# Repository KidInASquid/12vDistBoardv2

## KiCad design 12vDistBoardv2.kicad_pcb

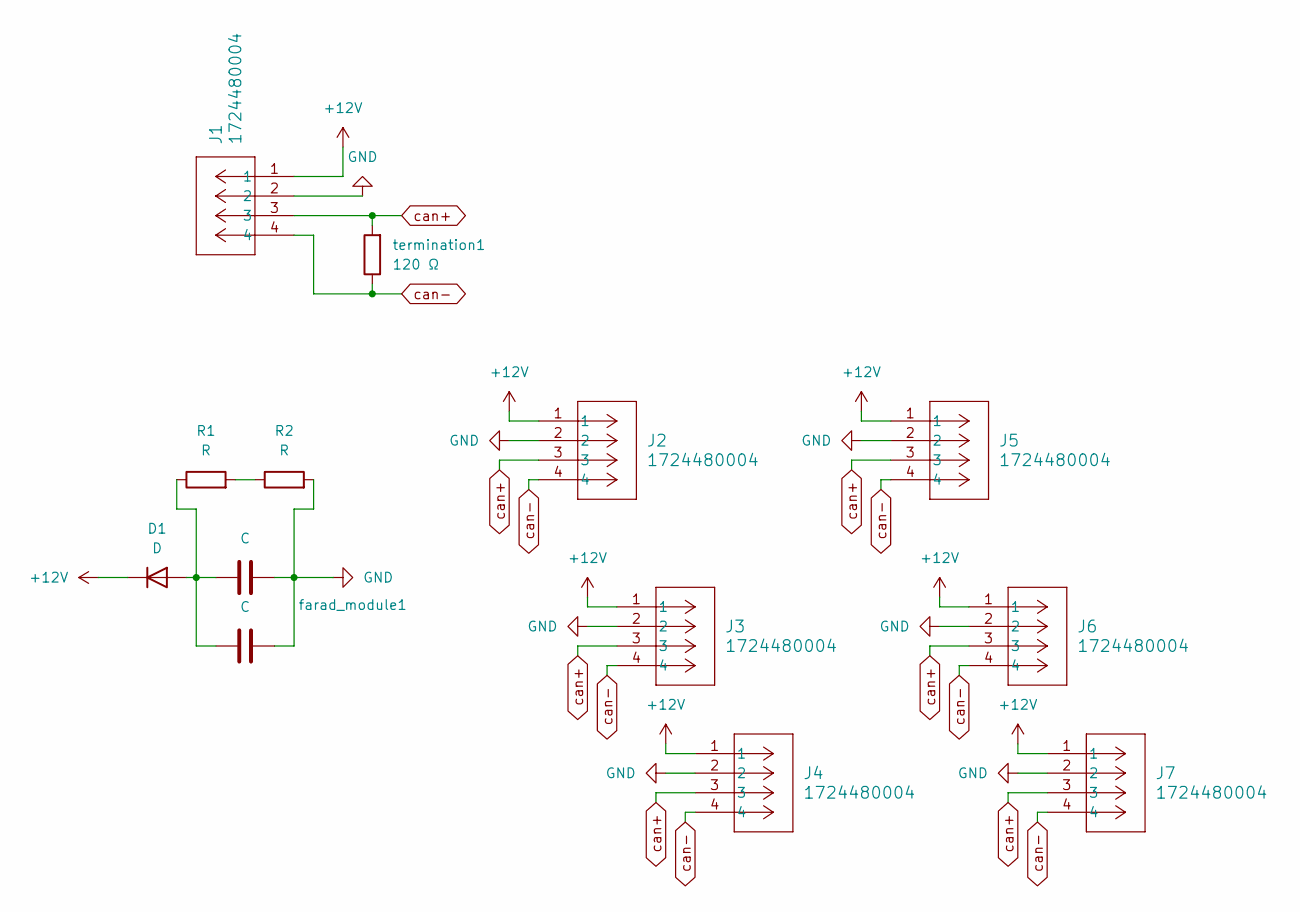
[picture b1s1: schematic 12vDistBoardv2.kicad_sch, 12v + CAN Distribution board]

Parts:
D1: D; D_SOD-123
J1, J2, J3, J4, J5, J6, J7: 1724480004; CON_1724480004
R1, R2: R; R_1210_3225Metric
farad_module1, farad_module2: C; C_Radial_D10.0mm_H20.0mm_P5.00mm
termination1: 120 Ω; R_0805_2012Metric

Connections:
+12V: D1.1 (K), J1.1, J2.1, J3.1, J4.1, J5.1, J6.1, J7.1; also elsewhere on the board
GND: J1.2, J2.2, J3.2, J4.2, J5.2, J6.2, J7.2, R2.2, farad_module1.1, farad_module2.1; also elsewhere on the board
unnamed: D1.2 (A), R1.1, farad_module1.2, farad_module2.2
unnamed: R1.2, R2.1
can+: J1.3, J2.3, J3.3, J4.3, J5.3, J6.3, J7.3, termination1.2; also elsewhere on the board
can-: J1.4, J2.4, J3.4, J4.4, J5.4, J6.4, J7.4, termination1.1; also elsewhere on the board

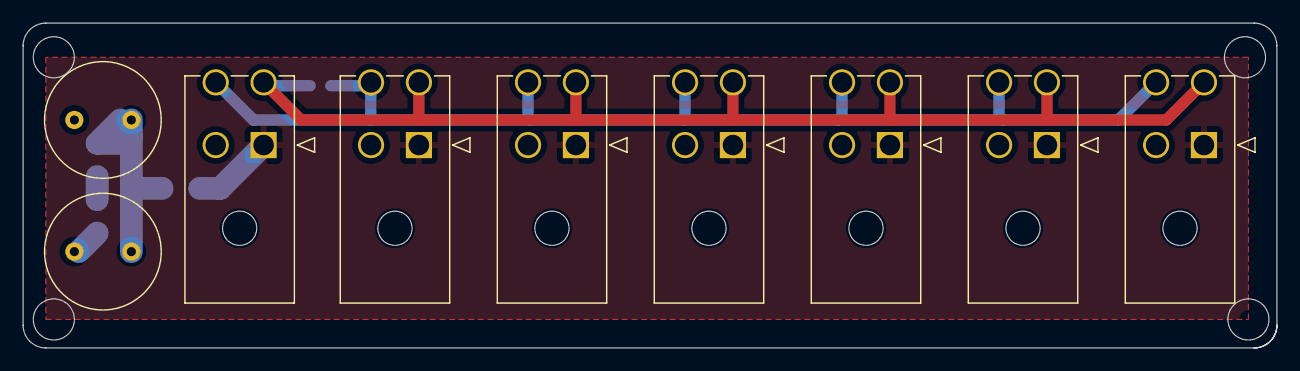
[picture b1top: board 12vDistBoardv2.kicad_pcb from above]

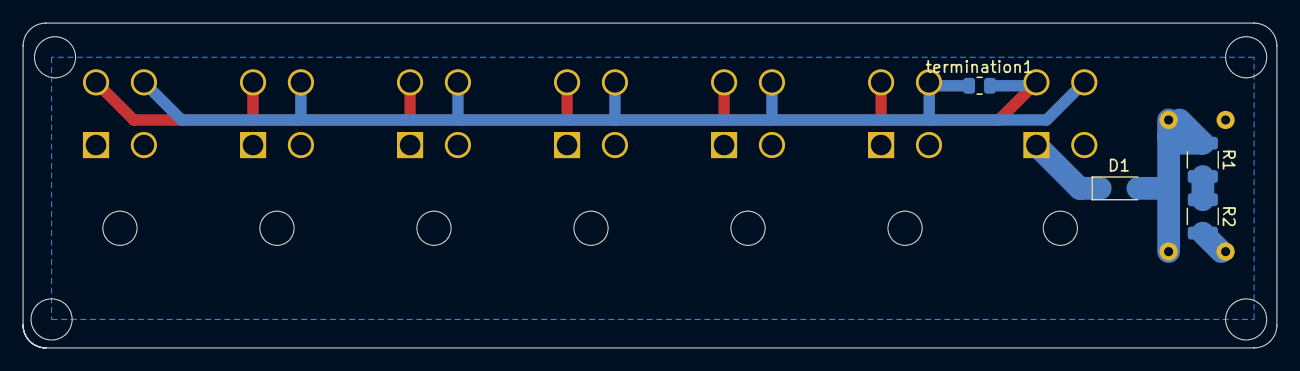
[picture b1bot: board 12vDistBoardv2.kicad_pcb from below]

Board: 2 copper layers, 110.0 x 28.5 mm, 13 parts (4 on the bottom side), 6 nets.

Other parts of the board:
J0: 1724480004; CON_1724480004

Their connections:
+12V: J0.1; also elsewhere on the board
GND: J0.2; also elsewhere on the board
can+: J0.3; also elsewhere on the board
can-: J0.4; also elsewhere on the board
